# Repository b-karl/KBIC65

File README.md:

# KBIC65
A 65% [mechanical keyboard](https://keyboard.university/100-courses/intro-to-mechanical-keyboards) with a [ProMicro](https://deskthority.net/wiki/Arduino_Pro_Micro) controller footprint. Repository contains [KiCad](https://www.kicad.org/) PCB design files and 2D drawings in SVG of PCB, bottom plate, switch plate and acrylic window.

Bottom of keyboard has two alternatives. A design with glass rims inspired by my grandfather's glasses and a dithered image of the sun from the [NASA Solar Dynamics Observatory](https://svs.gsfc.nasa.gov/13641). Included below is also a [guide on creating dithered PCB art](#making-dithered-pcb-art-for-kicad).

[More photos](img/photoshoot/readme.md)

# Main features/focus
- Intended to be portable and wireless, but with a [through-hole technology (THT)](https://en.wikipedia.org/wiki/Through-hole_technology) style
- 65%/70 key layout with spaced arrow keys and right-side navigation row in the style of [Satistifaction75](https://cannonkeys.com/collections/group-buy/products/gb-satisfaction-75-keyboard-round-2) and many others
- ProMicro footprint to allow upgrade of the microcontroller, intended to be used with the [nice!nano](https://nicekeyboards.com/nice-nano/) and [ZMK](https://zmkfirmware.dev/) firmware for my personal build
- Designed to be mountable in both an open PCB stack or in a plate-mounted case (not yet designed)
- 8x9 wiring [duplex matrix](https://wiki.ai03.com/books/pcb-design/page/matrices-and-duplex-matrix) requiring only 17 pins on a ProMicro compatible controller

# Some design choices

- Reduced copper coverage on top of PCB and bottom plate, and no copper switch plate to improve Bluetooth signal
- Plate mounted with screws, the PCB contains drilled holes large enough to fit M2 spacers. I.e. the PCB is only connected to the plate via the switches.
- Tried to avoid vias, but have one (that I probably could have skipped)
- Since the bottom is symmetrical, there are two alternative design two choose from

# How to create your own
[See the v1.0 release](https://github.com/b-karl/KBIC65/releases/tag/v1.0.0) to find the files and list of parts to create your own. 
- Gerber zip-files are used to order the PCB, bottom plate and top plate from a PCB manufacturer, I used [JLCPCB](https://jlcpcb.com/). 
- The acrylic window can be ordered from any laser cutting firm working with acrylic, I live in Sweden and used [TechStation](https://techstation.se/en/). 
- For keycaps, switches and ProMicro-compatible controller (possibly also diodes) use a keyboard company in your region, I got my keycaps from [KBDfans](https://kbdfans.com/), diodes from a local electronics supplier and the rest from [Splitkb](https://splitkb.com/).
- Screws and stand-offs can be sourced from various places but are probably easiest to find on AliExpress.

I do not have dedicated assembly instructions, but if you are comfortable soldering you can probably make do using [my build log](build_log.md).
# Firmware
I decided to use [ZMK](https://zmkfirmware.dev/) for my build of this keyboard. Compared to the most common open source mechanical keyboard firmware [QMK](https://docs.qmk.fm/#/), ZMK is tailored for wireless keyboards. The two main reasons you should care to use ZMK instead of a bluetooth QMK fork are (1) much better power efficiency, i.e. longer battery life, and (2) the most commonly used Bluetooth chip uses drivers that are not compatible with the QMK copyleft license.

You can find my ZMK shield for the KBIC65 in [my ZMK config repository](https://github.com/b-karl/zmk-config).

If you want to use a non-wireless controller (like a ProMicro, Elite-C etc.), I have [created a QMK fork](https://github.com/b-karl/qmk_firmware/tree/add-kbic65-keyboard/keyboards/karlb/kbic65) that has been tested on the KBIC65 using an Elite-C rev 4.

# Layout options

# Components

## PCB Front

## Plate

## Bottom Option 1 (PCB Front)

## Bottom Option 2 (PCB Back)

# Making dithered PCB art for KiCad
When I decided to make an alternative design for the bottom I eventually settled on trying my hand at a dithered image. This was a little trickier than I expected to get looking like I wanted (and still not sure how the end result will appear).

But generally here is the workflow I used in the end, and would recommend
- Settle on an image to use, crop it to only the part you want to place on the PCB. I settled on a NASA SDO image.

- JLCPCB and probably other PCB manufacturers can print at a resolution of about 0.15 mm which is equivalent to about 169 DPI. This means you should try to use 169 DPI or less, I used 169 DPI. Resize your image so that the resolution of the image at your selected DPI gives you the size you want on the board. I wanted my sun to be approximately 90 mm high so I resized to 600px high, which results in an image 90.2 mm high at 169 DPI. 

- Use a dithering tool to dither your image and create a dithered copy. I strongly recommend [Ditherlicious](https://29a.ch/ditherlicious/) but you can look around for other tools you have handy.

- Open your KiCad project and then open Convert Image, a.k.a. the bitmap2component tool.
- Import your dithered image, select Negative if necessary, pick either Front Silk Screen or Front Solder Mask and enter your chosen DPI. Click export and put into a new folder that will become a new KiCad library for you.
- In Pcbnew or your KiCad project, open Preferences > Manage footprint libraries
- Add your new folder as a footprint library
- Import your new PCB art footprint onto your PCB

- Iterate, I played a lot with different dithering tools, changing the image histogram etc. The bitmap2component tool does not import dithered image exactly but blends pixels together, therefore I would recommend generating a few variants and comparing them in KiCad and possibly the 3D viewer. Please note that these images requires quite a bit of processing from KiCad. Updating the 3D view especially, which took about 1-2 min for me.

- Final result after ordering from JLCPCB with black solder mask and ENIG finish

# Comparison to similar keyboards

## Discipline65
The [Discipline65](https://github.com/coseyfannitutti/discipline) is the original inspiration for this keyboard, along with the case making community that has been born around it. In the spirit of CFTKB the board design will also be open source.

Some of the main differences
- KBIC65 will use a dedicated ProMicro footprint instead of all the THT components in the Discipline65, a believe this makes the board more easy to upgrade at the cost of losing some of the THT aesthetic.
- The layers in the Discipline FR4 kit have the same outer dimension (excluding the top part of the plate), which is nice for a pure FR4-style keyboard but creates some limitations if one wants to create a case for it. The KBIC65 will have a minimal PCB given the layout (on the left, bottom and right sides) and a plate with overhang allowing for various types of plate-mounted case designs.
- The PCB will have holes large enough to fit M2 spacers between THT row and the layout. This allows the FR4 kit-style assembly to have the PCB completely free-floating and only the switch plate connecting directly to the bottom plate.

## Nibble65
The [Nibble65](https://nullbits.co/nibble/) is another board inspired by the Discipline65. It has an additional column of keys on the left, allowing also for rotary encoders and the top of this column houses a ProMicro footprint. 

Some differences
- The Nibble65 has similar limitations to the Discipline65 in terms of case design compatibility
- The Nibble65 uses multiplexers (I believe) to keep the PCB wiring simple and to add a bit to the THT aesthetic. The KBIC65 uses an efficient wiring matrix allowing for a full 65%/70 key layout without additional components.
- The Nibble65 has an extra column to the left, housing a ProMicro-footprint, some extra keys as well as a multi-purpose section for either rotary encodes, giant LED or an OLED screen.

# Possible future work
- Non-metal case
- Solar cell trickle charging panel instead of window
- Remove unintended silk screen from front PCB glasses
- Add holes for mounting a battery connector
- Move JLCPCB production number location (or get it removed in production)
- Change battery to something slightly thinner, sub-5 mm, but could be wider and longer than the current battery

# FAQ

### What does KBIC mean?
The original name KBIC65 is inspired by soldering and tinkering in my grandfather's workshop as a child and have named it with our combined initials KB and IC. But having spent quite a bit of time on making PCB art for the bottom of the keyboard based on an image from the [NASA Solar Dynamics Observatory](https://svs.gsfc.nasa.gov/13641) I am considering renaming it if I make anything more of it (or make a group buy at some point). I am open to name suggestions if you have one!

### Why don't you just buy keyboard X? It is cheaper and simpler than designing this.
I am doing this as a side project for fun, and the learning experience, and definitely not for profit.

If you want a 65% keyboard with the THT aesthetic get a [Discipline65](https://github.com/coseyfannitutti/discipline). If you want a 65% for your nice!nano, get the [Nibble65](https://nullbits.co/nibble/). If you just want something wireless but don't want to build it yourself, get a [Keychron](https://www.keychron.com/).

### I really want to make one myself, can you please fix the remaining issues?
Maybe, if you have some experience or willingness to learn, fork this repo and try to fix it yourself (and maybe do a PR on the end result). If you don't have the experience or know-how, send me a message so I know someone actually wants it and I will consider fixing it when I have time.

### This is just a rip-off of keyboard X. What gives?
I am trying to make my own thing but the design is of course heavily inspired by other keyboards, especially THT kits. Some honorable mentions

- [Nicell Dissatisfaction65](https://github.com/Nicell/Dissatisfaction-65)
A very similar keyboard to what I am designing, by the creator of the nice!nano. This uses a lot of the "early" techniques for what I feel a wireless open-source firmware was in 2019-beginning of 2020 such as Adafruit Feather BLE with QMK, something that is much better done today with the nice!nano (and similar controllers) and the ZMK firmware. Nicell is the creator of the nice!nano and also very active in the ZMK project.

- [CannonKeys Satisfaction75](https://ilumkb.com/blogs/news/satisfaction-75-r2)
My original inspiration for the layout

- [CFTKB Discipline65](https://github.com/coseyfannitutti/discipline)
Original inspiration for the THT design and the idea to make an FR4 kit first and a case after. The open-source Kicad files have also been a good sanity check, plus it has beautiful wiring!

- [Nullbits Nibble65](https://nullbits.co/nibble/)
A great take on the THT and would be my choice to buy if I didn't want to make something of my own but still make a nice!nano keyboard.

- [Lysol LCK75](https://p3dstore.com/products/lck75): No diode row but THT components otherwise and that arrow keys and navigation column stagger.

- [MujiManic Disarray65](https://sneakbox.com/products/disarray): Not exactly THT, but sooo much fun, beautiful wiring and one of the best case ideas ever. Case also comes in a version for the Discipline.

- [RMI-KB Herringbone75](https://rmi-kb.com/herringbone/): A fun variant on the Mysterium 75.

- [u/emdarcher Lattice 60%](https://keyhive.xyz/shop/lattice): Definitely contender for most innovative diode placement among THT keyboards

- [theksmith Discipline65](https://theksmith.com/hardware/designing-building-custom-mechanical-keyboard-2020/): Honorable mention on Discipline65 case design

- [4Bar60 by u/struct_Nodes](https://www.reddit.com/r/MechanicalKeyboards/comments/kyjpx3/my_girlfriend_surprised_me_with_a_breakup_before/)
I found this keyboard in the middle of my PCB design but it is very similar to my intended design, except being a 60% of course.

- [WorldspawnsKeebs Houndstooth](https://www.etsy.com/uk/listing/717316405/houndstooth-kit-does-not-include?show_sold_out_detail=1&ref=nla_listing_details)
A split ortholinear 4x6 with a nice take on a clear case

- [Seoulcialite Argyle60](https://geekhack.org/index.php?topic=106255.0)
Great case for a THT kit and very interesting with side windows instead of placed above the key layout. Inspiration for moving the ProMicro footprint and diode row up 1/4 units to allow top case to have a divider between main layout and THT window.

- [EBastler Isometria75](https://github.com/ebastler/isometria-75)
Makes me want to try to change the key spacing on my keyboard, but I am unfortunately not brave enough.

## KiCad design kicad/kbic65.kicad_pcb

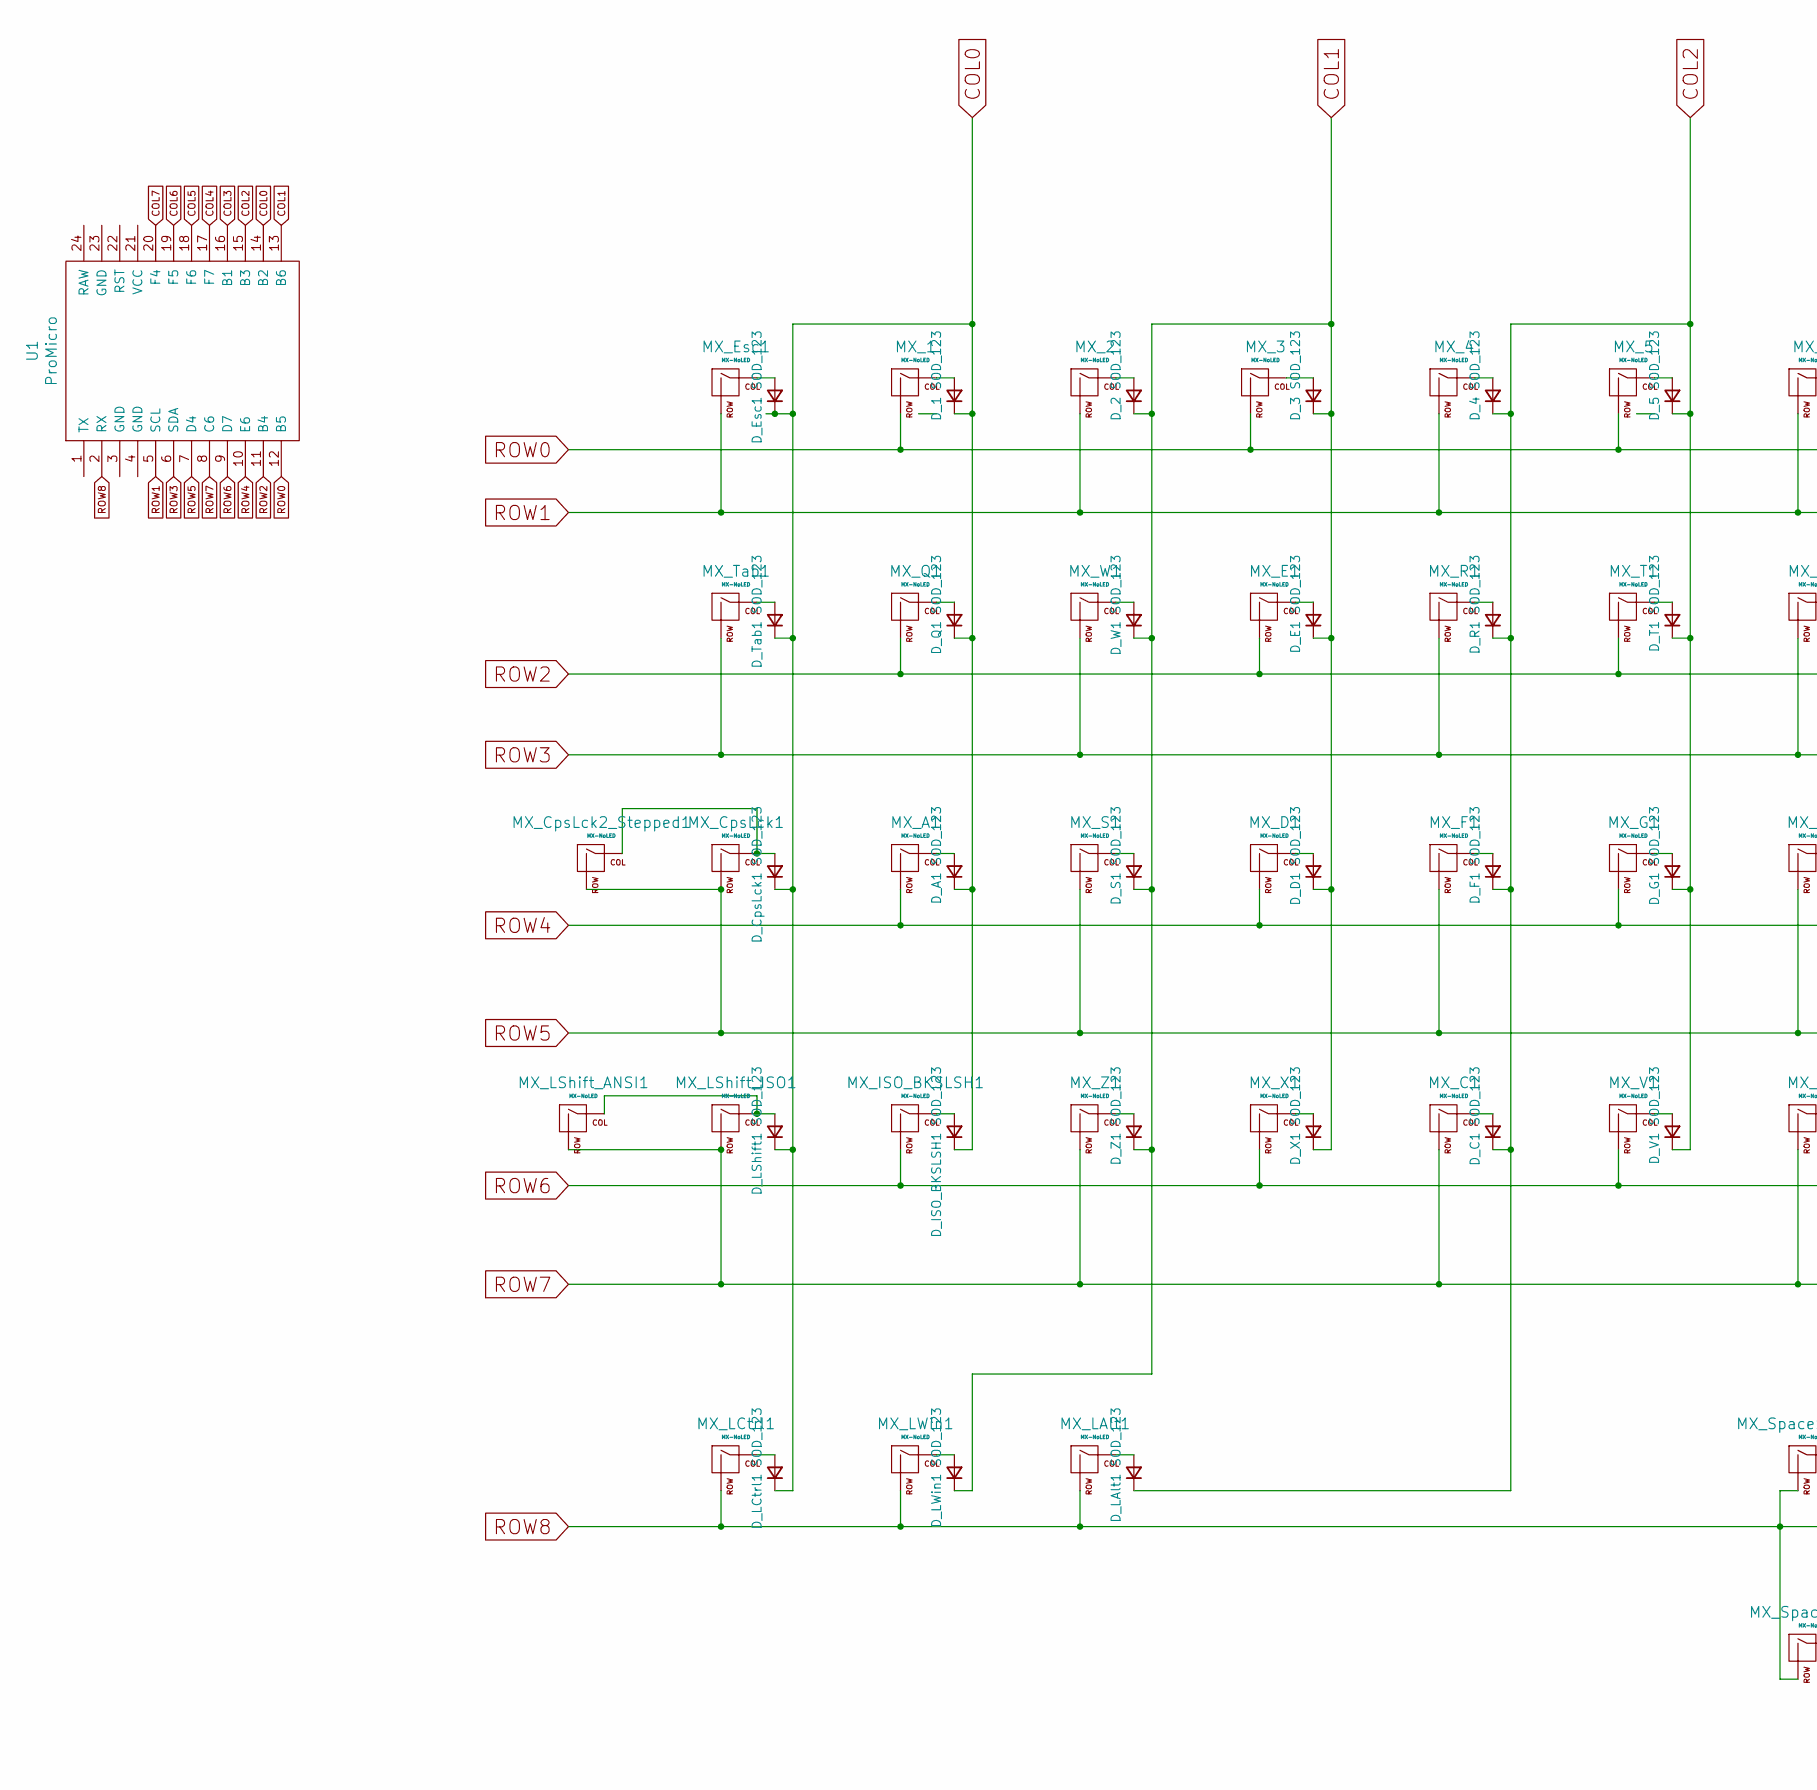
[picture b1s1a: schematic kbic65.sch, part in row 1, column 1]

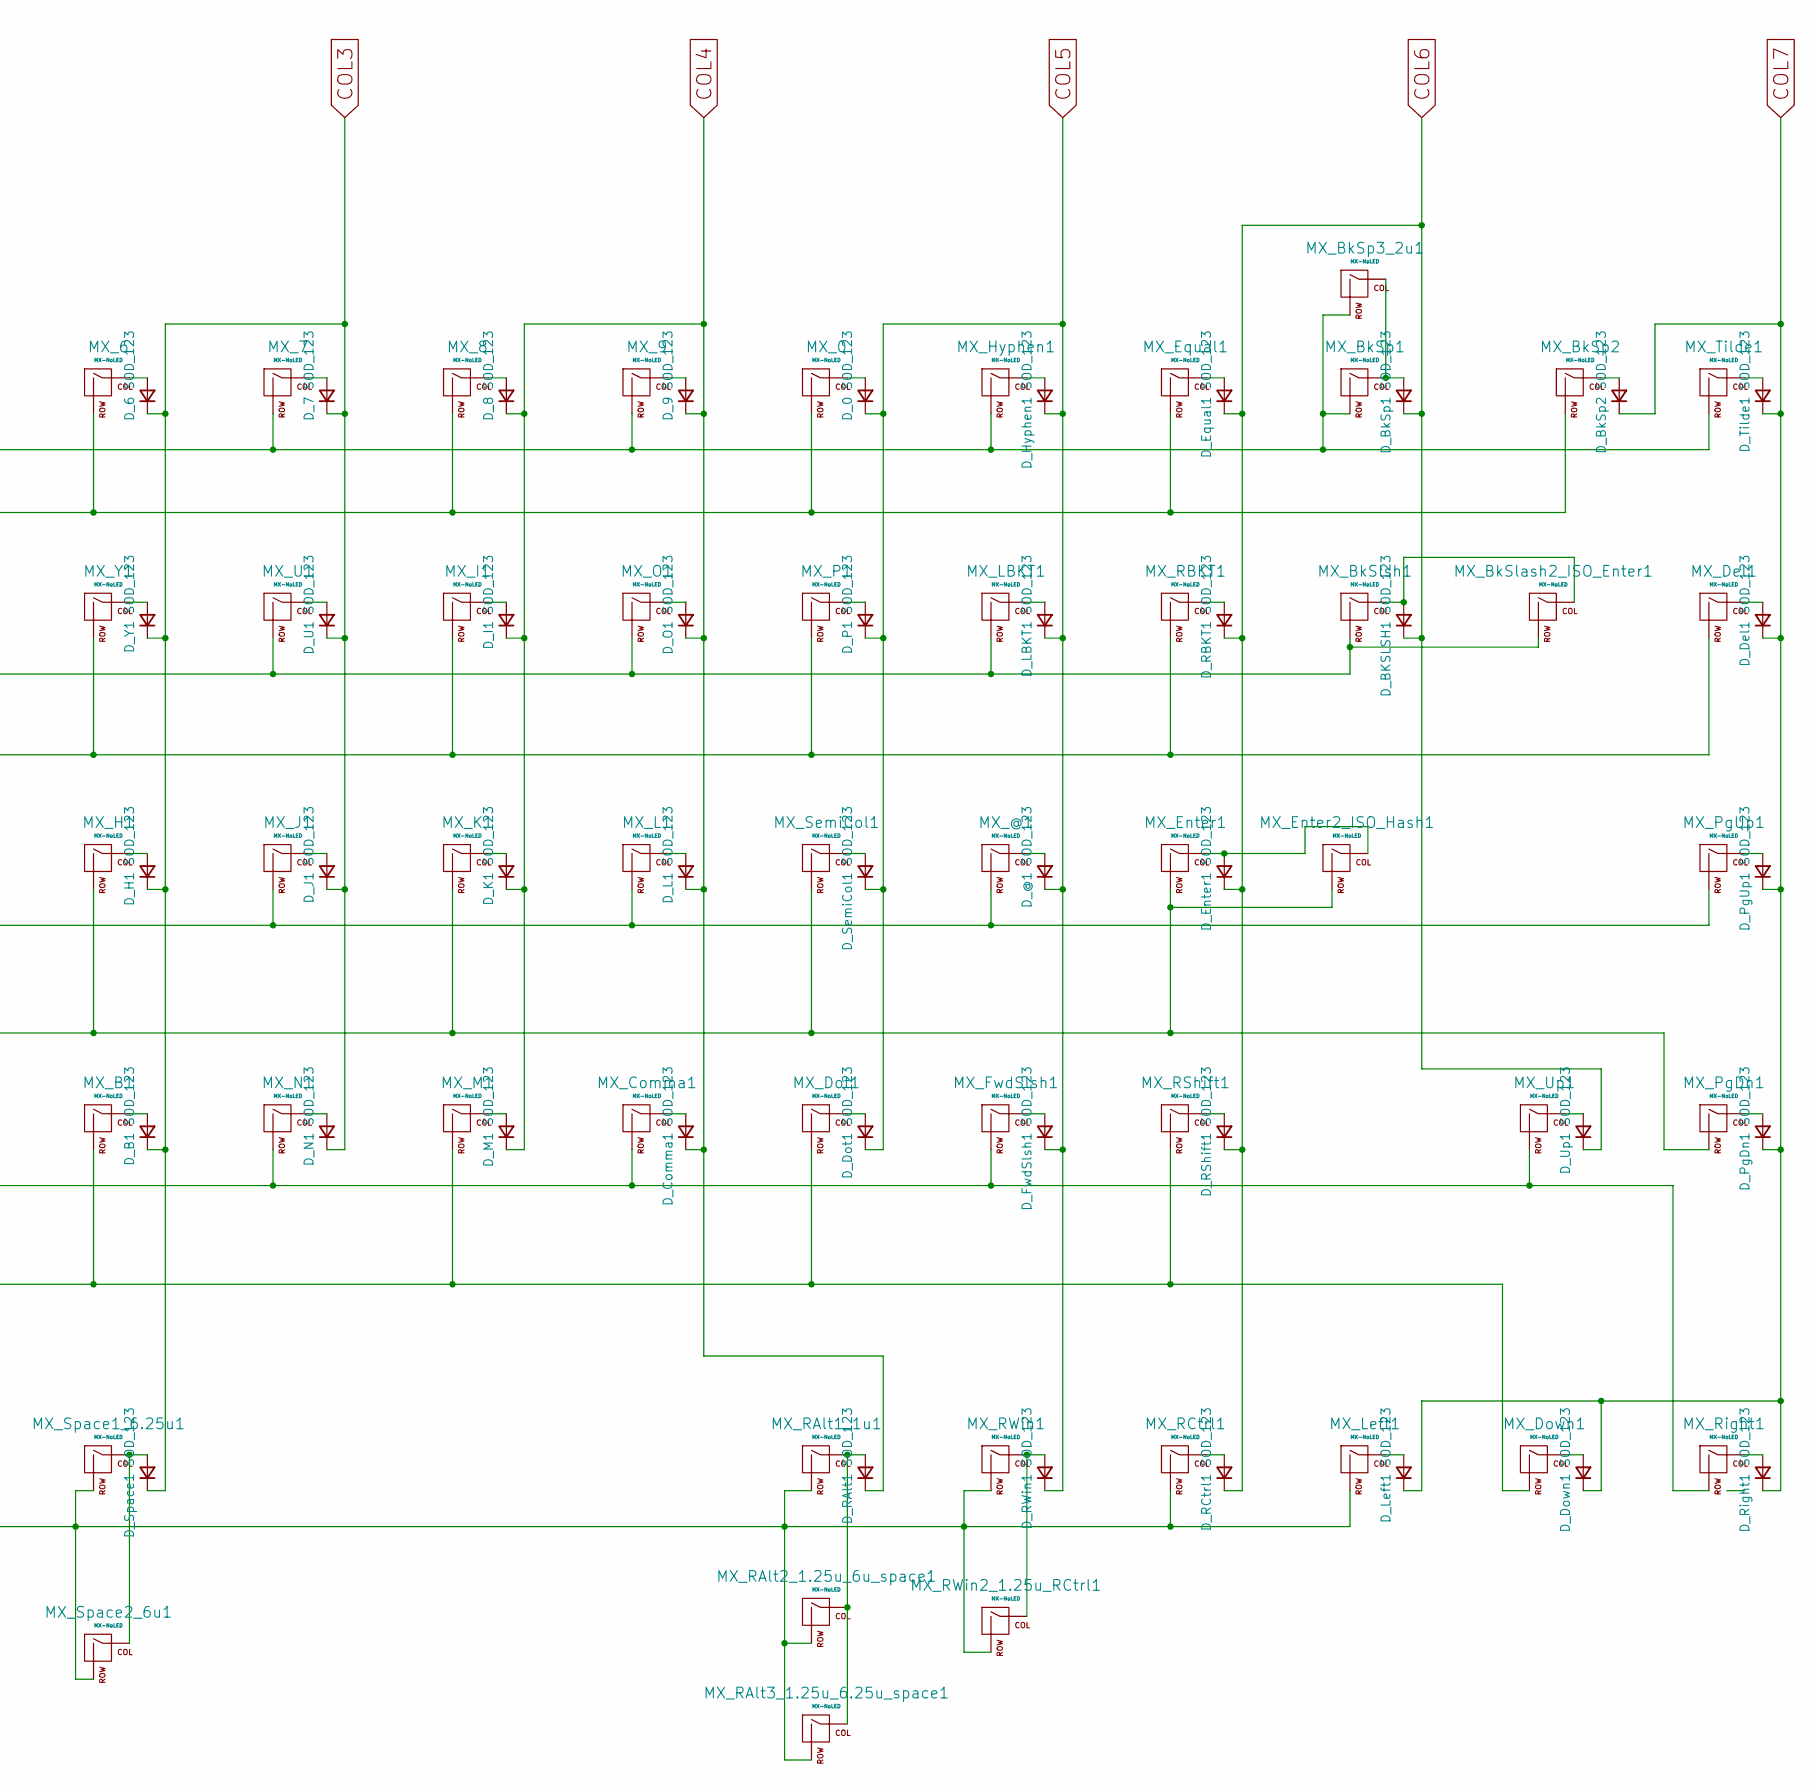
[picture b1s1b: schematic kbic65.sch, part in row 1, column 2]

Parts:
D_0, D_1, D_2, D_3, D_4, D_5, D_6, D_7, D_8, D_9: SOD_123; D_DO-35_SOD27_P5.08mm_Vertical_AnodeUp
D_@1: SOD_123; D_DO-35_SOD27_P5.08mm_Vertical_AnodeUp
D_A1: SOD_123; D_DO-35_SOD27_P5.08mm_Vertical_AnodeUp
D_B1: SOD_123; D_DO-35_SOD27_P5.08mm_Vertical_AnodeUp
D_BKSLSH1: SOD_123; D_DO-35_SOD27_P5.08mm_Vertical_AnodeUp
D_BkSp1, D_BkSp2: SOD_123; D_DO-35_SOD27_P5.08mm_Vertical_AnodeUp
D_C1: SOD_123; D_DO-35_SOD27_P5.08mm_Vertical_AnodeUp
D_Comma1: SOD_123; D_DO-35_SOD27_P5.08mm_Vertical_AnodeUp
D_CpsLck1: SOD_123; D_DO-35_SOD27_P5.08mm_Vertical_AnodeUp
D_D1: SOD_123; D_DO-35_SOD27_P5.08mm_Vertical_AnodeUp
D_Del1: SOD_123; D_DO-35_SOD27_P5.08mm_Vertical_AnodeUp
D_Dot1: SOD_123; D_DO-35_SOD27_P5.08mm_Vertical_AnodeUp
D_Down1: SOD_123; D_DO-35_SOD27_P5.08mm_Vertical_AnodeUp
D_E1: SOD_123; D_DO-35_SOD27_P5.08mm_Vertical_AnodeUp
D_Enter1: SOD_123; D_DO-35_SOD27_P5.08mm_Vertical_AnodeUp
D_Equal1: SOD_123; D_DO-35_SOD27_P5.08mm_Vertical_AnodeUp
D_Esc1: SOD_123; D_DO-35_SOD27_P5.08mm_Vertical_AnodeUp
D_F1: SOD_123; D_DO-35_SOD27_P5.08mm_Vertical_AnodeUp
D_FwdSlsh1: SOD_123; D_DO-35_SOD27_P5.08mm_Vertical_AnodeUp
D_G1: SOD_123; D_DO-35_SOD27_P5.08mm_Vertical_AnodeUp
D_H1: SOD_123; D_DO-35_SOD27_P5.08mm_Vertical_AnodeUp
D_Hyphen1: SOD_123; D_DO-35_SOD27_P5.08mm_Vertical_AnodeUp
D_I1: SOD_123; D_DO-35_SOD27_P5.08mm_Vertical_AnodeUp
D_ISO_BKSLSH1: SOD_123; D_DO-35_SOD27_P5.08mm_Vertical_AnodeUp
D_J1: SOD_123; D_DO-35_SOD27_P5.08mm_Vertical_AnodeUp
D_K1: SOD_123; D_DO-35_SOD27_P5.08mm_Vertical_AnodeUp
D_L1: SOD_123; D_DO-35_SOD27_P5.08mm_Vertical_AnodeUp
D_LAlt1: SOD_123; D_DO-35_SOD27_P5.08mm_Vertical_AnodeUp
D_LBKT1: SOD_123; D_DO-35_SOD27_P5.08mm_Vertical_AnodeUp
D_LCtrl1: SOD_123; D_DO-35_SOD27_P5.08mm_Vertical_AnodeUp
D_LShift1: SOD_123; D_DO-35_SOD27_P5.08mm_Vertical_AnodeUp
D_LWin1: SOD_123; D_DO-35_SOD27_P5.08mm_Vertical_AnodeUp
D_Left1: SOD_123; D_DO-35_SOD27_P5.08mm_Vertical_AnodeUp
D_M1: SOD_123; D_DO-35_SOD27_P5.08mm_Vertical_AnodeUp
D_N1: SOD_123; D_DO-35_SOD27_P5.08mm_Vertical_AnodeUp
D_O1: SOD_123; D_DO-35_SOD27_P5.08mm_Vertical_AnodeUp
D_P1: SOD_123; D_DO-35_SOD27_P5.08mm_Vertical_AnodeUp
D_PgDn1: SOD_123; D_DO-35_SOD27_P5.08mm_Vertical_AnodeUp
D_PgUp1: SOD_123; D_DO-35_SOD27_P5.08mm_Vertical_AnodeUp
D_Q1: SOD_123; D_DO-35_SOD27_P5.08mm_Vertical_AnodeUp
D_R1: SOD_123; D_DO-35_SOD27_P5.08mm_Vertical_AnodeUp
D_RAlt1: SOD_123; D_DO-35_SOD27_P5.08mm_Vertical_AnodeUp
D_RBKT1: SOD_123; D_DO-35_SOD27_P5.08mm_Vertical_AnodeUp
D_RCtrl1: SOD_123; D_DO-35_SOD27_P5.08mm_Vertical_AnodeUp
D_RShift1: SOD_123; D_DO-35_SOD27_P5.08mm_Vertical_AnodeUp
D_RWin1: SOD_123; D_DO-35_SOD27_P5.08mm_Vertical_AnodeUp
D_Right1: SOD_123; D_DO-35_SOD27_P5.08mm_Vertical_AnodeUp
D_S1: SOD_123; D_DO-35_SOD27_P5.08mm_Vertical_AnodeUp
D_SemiCol1: SOD_123; D_DO-35_SOD27_P5.08mm_Vertical_AnodeUp
D_Space1: SOD_123; D_DO-35_SOD27_P5.08mm_Vertical_AnodeUp
D_T1: SOD_123; D_DO-35_SOD27_P5.08mm_Vertical_AnodeUp
D_Tab1: SOD_123; D_DO-35_SOD27_P5.08mm_Vertical_AnodeUp
D_Tilde1: SOD_123; D_DO-35_SOD27_P5.08mm_Vertical_AnodeUp
D_U1: SOD_123; D_DO-35_SOD27_P5.08mm_Vertical_AnodeUp
D_Up1: SOD_123; D_DO-35_SOD27_P5.08mm_Vertical_AnodeUp
D_V1: SOD_123; D_DO-35_SOD27_P5.08mm_Vertical_AnodeUp
D_W1: SOD_123; D_DO-35_SOD27_P5.08mm_Vertical_AnodeUp
D_X1: SOD_123; D_DO-35_SOD27_P5.08mm_Vertical_AnodeUp
D_Y1: SOD_123; D_DO-35_SOD27_P5.08mm_Vertical_AnodeUp
D_Z1: SOD_123; D_DO-35_SOD27_P5.08mm_Vertical_AnodeUp
MX_0, MX_1, MX_2, MX_3, MX_4, MX_5, MX_6, MX_7, MX_8, MX_9: MX-NoLED; MXOnly-1U-NoLED
MX_@1: MX-NoLED; MXOnly-1U-NoLED
MX_A1: MX-NoLED; MXOnly-1U-NoLED
MX_B1: MX-NoLED; MXOnly-1U-NoLED
MX_BkSlash2_ISO_Enter1: MX-NoLED; MXOnly-ISO-ROTATED-ReversedStabilizers-NoLED
MX_BkSlsh1: MX-NoLED; MXOnly-1.5U-NoLED
MX_BkSp1, MX_BkSp2: MX-NoLED; MXOnly-1U-NoLED
MX_BkSp3_2u1: MX-NoLED; MXOnly-2U-NoLED
MX_C1: MX-NoLED; MXOnly-1U-NoLED
MX_Comma1: MX-NoLED; MXOnly-1U-NoLED
MX_CpsLck1: MX-NoLED; MXOnly-1.75U-NoLED
MX_CpsLck2_Stepped1: MX-NoLED; MXOnly-1.25U-NoLED
MX_D1: MX-NoLED; MXOnly-1U-NoLED
MX_Del1: MX-NoLED; MXOnly-1U-NoLED
MX_Dot1: MX-NoLED; MXOnly-1U-NoLED
MX_Down1: MX-NoLED; MXOnly-1U-NoLED
MX_E1: MX-NoLED; MXOnly-1U-NoLED
MX_Enter1: MX-NoLED; MXOnly-2.25U-NoLED
MX_Enter2_ISO_Hash1: MX-NoLED; MXOnly-1U-NoLED
MX_Equal1: MX-NoLED; MXOnly-1U-NoLED
MX_Esc1: MX-NoLED; MXOnly-1U-NoLED
MX_F1: MX-NoLED; MXOnly-1U-NoLED
MX_FwdSlsh1: MX-NoLED; MXOnly-1U-NoLED
MX_G1: MX-NoLED; MXOnly-1U-NoLED
MX_H1: MX-NoLED; MXOnly-1U-NoLED
MX_Hyphen1: MX-NoLED; MXOnly-1U-NoLED
MX_I1: MX-NoLED; MXOnly-1U-NoLED
MX_ISO_BKSLSH1: MX-NoLED; MXOnly-1U-NoLED
MX_J1: MX-NoLED; MXOnly-1U-NoLED
MX_K1: MX-NoLED; MXOnly-1U-NoLED
MX_L1: MX-NoLED; MXOnly-1U-NoLED
MX_LAlt1: MX-NoLED; MXOnly-1.25U-NoLED
MX_LBKT1: MX-NoLED; MXOnly-1U-NoLED
MX_LCtrl1: MX-NoLED; MXOnly-1.25U-NoLED
MX_LShift_ANSI1: MX-NoLED; MXOnly-2.25U-NoLED
MX_LShift_ISO1: MX-NoLED; MXOnly-1.25U-NoLED
MX_LWin1: MX-NoLED; MXOnly-1.25U-NoLED
MX_Left1: MX-NoLED; MXOnly-1U-NoLED
MX_M1: MX-NoLED; MXOnly-1U-NoLED
MX_N1: MX-NoLED; MXOnly-1U-NoLED
MX_O1: MX-NoLED; MXOnly-1U-NoLED
MX_P1: MX-NoLED; MXOnly-1U-NoLED
MX_PgDn1: MX-NoLED; MXOnly-1U-NoLED
MX_PgUp1: MX-NoLED; MXOnly-1U-NoLED
MX_Q1: MX-NoLED; MXOnly-1U-NoLED
MX_R1: MX-NoLED; MXOnly-1U-NoLED
MX_RAlt1_1u1: MX-NoLED; MXOnly-1U-NoLED
MX_RAlt2_1.25u_6u_space1, MX_RAlt3_1.25u_6.25u_space1: MX-NoLED; MXOnly-1.25U-NoLED
MX_RBKT1: MX-NoLED; MXOnly-1U-NoLED
MX_RCtrl1: MX-NoLED; MXOnly-1U-NoLED
MX_RShift1: MX-NoLED; MXOnly-1.75U-NoLED
MX_RWin1, MX_RWin2_1.25u_RCtrl1: MX-NoLED; MXOnly-1U-NoLED
MX_Right1: MX-NoLED; MXOnly-1U-NoLED
MX_S1: MX-NoLED; MXOnly-1U-NoLED
MX_SemiCol1: MX-NoLED; MXOnly-1U-NoLED
MX_Space1_6.25u1: MX-NoLED; MXOnly-6.25U-NoLED
MX_Space2_6u1: MX-NoLED; MXOnly-6U-Centered-NoLED
MX_T1: MX-NoLED; MXOnly-1U-NoLED
MX_Tab1: MX-NoLED; MXOnly-1.5U-NoLED
MX_Tilde1: MX-NoLED; MXOnly-1U-NoLED
MX_U1: MX-NoLED; MXOnly-1U-NoLED
MX_Up1: MX-NoLED; MXOnly-1U-NoLED
MX_V1: MX-NoLED; MXOnly-1U-NoLED
MX_W1: MX-NoLED; MXOnly-1U-NoLED
MX_X1: MX-NoLED; MXOnly-1U-NoLED
MX_Y1: MX-NoLED; MXOnly-1U-NoLED
MX_Z1: MX-NoLED; MXOnly-1U-NoLED
U1: ProMicro; ArduinoProMicro-ZigZag

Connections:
COL0: D_1.1 (K), D_A1.1 (K), D_CpsLck1.1 (K), D_Esc1.1 (K), D_ISO_BKSLSH1.1 (K), D_LCtrl1.1 (K), D_LShift1.1 (K), D_Q1.1 (K), D_Tab1.1 (K), U1.14 (B2)
COL1: D_2.1 (K), D_3.1 (K), D_D1.1 (K), D_E1.1 (K), D_LWin1.1 (K), D_S1.1 (K), D_W1.1 (K), D_X1.1 (K), D_Z1.1 (K), U1.13 (B6)
COL2: D_4.1 (K), D_5.1 (K), D_C1.1 (K), D_F1.1 (K), D_G1.1 (K), D_LAlt1.1 (K), D_R1.1 (K), D_T1.1 (K), D_V1.1 (K), U1.15 (B3)
COL3: D_6.1 (K), D_7.1 (K), D_B1.1 (K), D_H1.1 (K), D_J1.1 (K), D_N1.1 (K), D_Space1.1 (K), D_U1.1 (K), D_Y1.1 (K), U1.16 (B1)
COL4: D_8.1 (K), D_9.1 (K), D_Comma1.1 (K), D_I1.1 (K), D_K1.1 (K), D_L1.1 (K), D_M1.1 (K), D_O1.1 (K), D_RAlt1.1 (K), U1.17 (F7)
COL5: D_0.1 (K), D_@1.1 (K), D_Dot1.1 (K), D_FwdSlsh1.1 (K), D_Hyphen1.1 (K), D_LBKT1.1 (K), D_P1.1 (K), D_RWin1.1 (K), D_SemiCol1.1 (K), U1.18 (F6)
COL6: D_BKSLSH1.1 (K), D_BkSp1.1 (K), D_Enter1.1 (K), D_Equal1.1 (K), D_RBKT1.1 (K), D_RCtrl1.1 (K), D_RShift1.1 (K), D_Up1.1 (K), U1.19 (F5)
COL7: D_BkSp2.1 (K), D_Del1.1 (K), D_Down1.1 (K), D_Left1.1 (K), D_PgDn1.1 (K), D_PgUp1.1 (K), D_Right1.1 (K), D_Tilde1.1 (K), U1.20 (F4)
GND: U1.3 (GND), U1.4 (GND), U1.23 (GND)
unnamed: D_0.2 (A), MX_0.1 (COL)
unnamed: D_1.2 (A), MX_1.1 (COL)
unnamed: D_2.2 (A), MX_2.1 (COL)
unnamed: D_3.2 (A), MX_3.1 (COL)
unnamed: D_4.2 (A), MX_4.1 (COL)
unnamed: D_5.2 (A), MX_5.1 (COL)
unnamed: D_6.2 (A), MX_6.1 (COL)
unnamed: D_7.2 (A), MX_7.1 (COL)
unnamed: D_8.2 (A), MX_8.1 (COL)
unnamed: D_9.2 (A), MX_9.1 (COL)
unnamed: D_@1.2 (A), MX_@1.1 (COL)
unnamed: D_A1.2 (A), MX_A1.1 (COL)
unnamed: D_B1.2 (A), MX_B1.1 (COL)
unnamed: D_BKSLSH1.2 (A), MX_BkSlash2_ISO_Enter1.1 (COL), MX_BkSlsh1.1 (COL)
unnamed: D_BkSp1.2 (A), MX_BkSp1.1 (COL), MX_BkSp3_2u1.1 (COL)
unnamed: D_BkSp2.2 (A), MX_BkSp2.1 (COL)
unnamed: D_C1.2 (A), MX_C1.1 (COL)
unnamed: D_Comma1.2 (A), MX_Comma1.1 (COL)
unnamed: D_CpsLck1.2 (A), MX_CpsLck1.1 (COL), MX_CpsLck2_Stepped1.1 (COL)
unnamed: D_D1.2 (A), MX_D1.1 (COL)
unnamed: D_Del1.2 (A), MX_Del1.1 (COL)
unnamed: D_Dot1.2 (A), MX_Dot1.1 (COL)
unnamed: D_Down1.2 (A), MX_Down1.1 (COL)
unnamed: D_E1.2 (A), MX_E1.1 (COL)
unnamed: D_Enter1.2 (A), MX_Enter1.1 (COL), MX_Enter2_ISO_Hash1.1 (COL)
unnamed: D_Equal1.2 (A), MX_Equal1.1 (COL)
unnamed: D_Esc1.2 (A), MX_Esc1.1 (COL)
unnamed: D_F1.2 (A), MX_F1.1 (COL)
unnamed: D_FwdSlsh1.2 (A), MX_FwdSlsh1.1 (COL)
unnamed: D_G1.2 (A), MX_G1.1 (COL)
unnamed: D_H1.2 (A), MX_H1.1 (COL)
unnamed: D_Hyphen1.2 (A), MX_Hyphen1.1 (COL)
unnamed: D_I1.2 (A), MX_I1.1 (COL)
unnamed: D_ISO_BKSLSH1.2 (A), MX_ISO_BKSLSH1.1 (COL)
unnamed: D_J1.2 (A), MX_J1.1 (COL)
unnamed: D_K1.2 (A), MX_K1.1 (COL)
unnamed: D_L1.2 (A), MX_L1.1 (COL)
unnamed: D_LAlt1.2 (A), MX_LAlt1.1 (COL)
unnamed: D_LBKT1.2 (A), MX_LBKT1.1 (COL)
unnamed: D_LCtrl1.2 (A), MX_LCtrl1.1 (COL)
unnamed: D_LShift1.2 (A), MX_LShift_ANSI1.1 (COL), MX_LShift_ISO1.1 (COL)
unnamed: D_LWin1.2 (A), MX_LWin1.1 (COL)
unnamed: D_Left1.2 (A), MX_Left1.1 (COL)
unnamed: D_M1.2 (A), MX_M1.1 (COL)
unnamed: D_N1.2 (A), MX_N1.1 (COL)
unnamed: D_O1.2 (A), MX_O1.1 (COL)
unnamed: D_P1.2 (A), MX_P1.1 (COL)
unnamed: D_PgDn1.2 (A), MX_PgDn1.1 (COL)
unnamed: D_PgUp1.2 (A), MX_PgUp1.1 (COL)
unnamed: D_Q1.2 (A), MX_Q1.1 (COL)
unnamed: D_R1.2 (A), MX_R1.1 (COL)
unnamed: D_RAlt1.2 (A), MX_RAlt1_1u1.1 (COL), MX_RAlt2_1.25u_6u_space1.1 (COL), MX_RAlt3_1.25u_6.25u_space1.1 (COL)
unnamed: D_RBKT1.2 (A), MX_RBKT1.1 (COL)
unnamed: D_RCtrl1.2 (A), MX_RCtrl1.1 (COL)
unnamed: D_RShift1.2 (A), MX_RShift1.1 (COL)
unnamed: D_RWin1.2 (A), MX_RWin1.1 (COL), MX_RWin2_1.25u_RCtrl1.1 (COL)
unnamed: D_Right1.2 (A), MX_Right1.1 (COL)
unnamed: D_S1.2 (A), MX_S1.1 (COL)
unnamed: D_SemiCol1.2 (A), MX_SemiCol1.1 (COL)
unnamed: D_Space1.2 (A), MX_Space1_6.25u1.1 (COL), MX_Space2_6u1.1 (COL)
unnamed: D_T1.2 (A), MX_T1.1 (COL)
unnamed: D_Tab1.2 (A), MX_Tab1.1 (COL)
unnamed: D_Tilde1.2 (A), MX_Tilde1.1 (COL)
unnamed: D_U1.2 (A), MX_U1.1 (COL)
unnamed: D_Up1.2 (A), MX_Up1.1 (COL)
unnamed: D_V1.2 (A), MX_V1.1 (COL)
unnamed: D_W1.2 (A), MX_W1.1 (COL)
unnamed: D_X1.2 (A), MX_X1.1 (COL)
unnamed: D_Y1.2 (A), MX_Y1.1 (COL)
unnamed: D_Z1.2 (A), MX_Z1.1 (COL)
ROW0: MX_1.2 (ROW), MX_3.2 (ROW), MX_5.2 (ROW), MX_7.2 (ROW), MX_9.2 (ROW), MX_BkSp1.2 (ROW), MX_BkSp3_2u1.2 (ROW), MX_Hyphen1.2 (ROW), MX_Tilde1.2 (ROW), U1.12 (B5)
ROW1: MX_0.2 (ROW), MX_2.2 (ROW), MX_4.2 (ROW), MX_6.2 (ROW), MX_8.2 (ROW), MX_BkSp2.2 (ROW), MX_Equal1.2 (ROW), MX_Esc1.2 (ROW), U1.5 (SCL)
ROW2: MX_BkSlash2_ISO_Enter1.2 (ROW), MX_BkSlsh1.2 (ROW), MX_E1.2 (ROW), MX_LBKT1.2 (ROW), MX_O1.2 (ROW), MX_Q1.2 (ROW), MX_T1.2 (ROW), MX_U1.2 (ROW), U1.11 (B4)
ROW3: MX_Del1.2 (ROW), MX_I1.2 (ROW), MX_P1.2 (ROW), MX_R1.2 (ROW), MX_RBKT1.2 (ROW), MX_Tab1.2 (ROW), MX_W1.2 (ROW), MX_Y1.2 (ROW), U1.6 (SDA)
ROW4: MX_@1.2 (ROW), MX_A1.2 (ROW), MX_D1.2 (ROW), MX_G1.2 (ROW), MX_J1.2 (ROW), MX_L1.2 (ROW), MX_PgUp1.2 (ROW), U1.10 (E6)
ROW5: MX_CpsLck1.2 (ROW), MX_CpsLck2_Stepped1.2 (ROW), MX_Enter1.2 (ROW), MX_Enter2_ISO_Hash1.2 (ROW), MX_F1.2 (ROW), MX_H1.2 (ROW), MX_K1.2 (ROW), MX_PgDn1.2 (ROW), MX_S1.2 (ROW), MX_SemiCol1.2 (ROW), U1.7 (D4)
ROW6: MX_Comma1.2 (ROW), MX_FwdSlsh1.2 (ROW), MX_ISO_BKSLSH1.2 (ROW), MX_N1.2 (ROW), MX_Right1.2 (ROW), MX_Up1.2 (ROW), MX_V1.2 (ROW), MX_X1.2 (ROW), U1.9 (D7)
ROW7: MX_B1.2 (ROW), MX_C1.2 (ROW), MX_Dot1.2 (ROW), MX_Down1.2 (ROW), MX_LShift_ANSI1.2 (ROW), MX_LShift_ISO1.2 (ROW), MX_M1.2 (ROW), MX_RShift1.2 (ROW), MX_Z1.2 (ROW), U1.8 (C6)
ROW8: MX_LAlt1.2 (ROW), MX_LCtrl1.2 (ROW), MX_LWin1.2 (ROW), MX_Left1.2 (ROW), MX_RAlt1_1u1.2 (ROW), MX_RAlt2_1.25u_6u_space1.2 (ROW), MX_RAlt3_1.25u_6.25u_space1.2 (ROW), MX_RCtrl1.2 (ROW), MX_RWin1.2 (ROW), MX_RWin2_1.25u_RCtrl1.2 (ROW), MX_Space1_6.25u1.2 (ROW), MX_Space2_6u1.2 (ROW), U1.2 (RX)

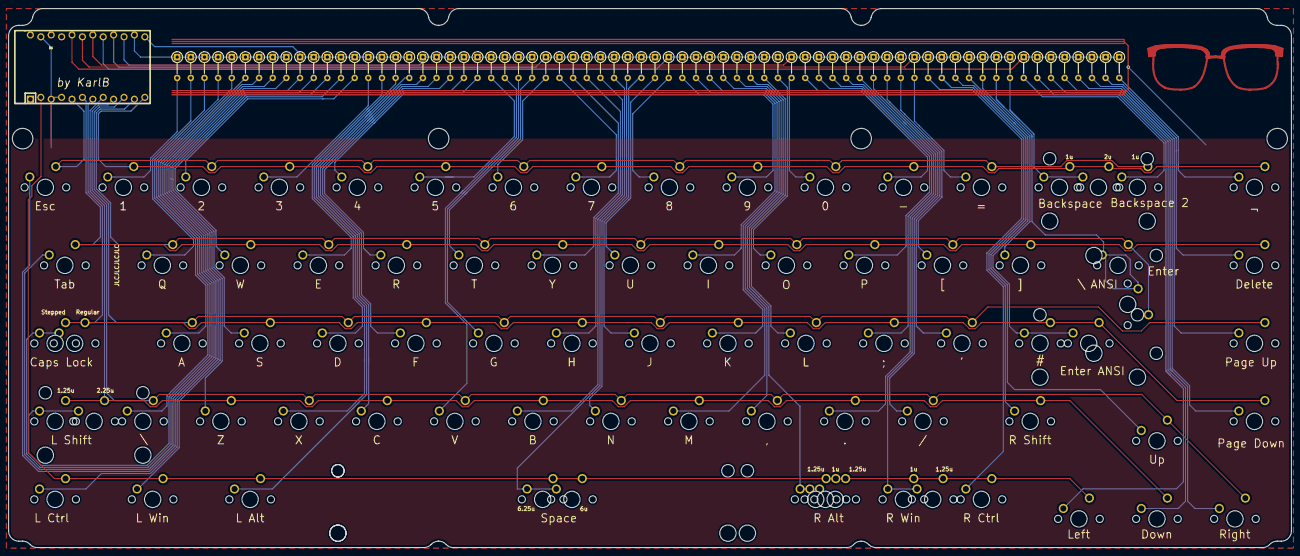
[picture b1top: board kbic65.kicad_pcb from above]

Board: 2 copper layers, 313.3 x 131.6 mm, 150 parts (0 on the bottom side), 88 nets.

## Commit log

2020-11-08 Created project
2020-11-08 Added submodules
2020-11-08 Added kebbio footprints
2020-11-08 added libraries to kicad
2020-11-08 added pro micro to kicad
2020-11-08 started working
2020-11-09 saved work in kicad
2020-12-07 Added key matrix
2020-12-12 Created new matrix and labeled ProMicro footprint
2020-12-12 Naming matrix components
2020-12-13 Added footprints
2020-12-14 Placed components on PCB and imported dxf
2020-12-14 Added and updated footprints
2020-12-16 Redrew schematic with all extra footprints
2020-12-16 Changed layout to top windows and rearranging diodes
2020-12-17 Changed diode to row2col instead to make better wiring, rearranging diode footprints
2020-12-19 Rearranged diodes for wiring
2020-12-19 Rearranged rows on promicro footprint
2020-12-19 Simple arrangement of diodes
2020-12-22 Reverted back to single line of diodes
2021-01-13 Changed outline to inkscape generated and aligned it
2021-01-13 Finally started wiring
2021-01-20 Changed structure of repo
2021-01-20 Added layout options
2021-01-20 Add isometria to readme
2021-01-20 More wiring
2021-01-21 Sooo much wiring
2021-01-22 Wiring 4 life
2021-01-22 added image
2021-01-23 Completed first version of full wiring
2021-01-24 Cleared wiring, starting over with default tracks
2021-01-24 Starting new wiring
2021-01-26 Updated wiring, added drill holes and cut outline
2021-01-27 Fixed 6u spacebar
2021-01-27 Moved drawings to git
2021-01-27 Merged all cutouts and added fillets in plate
2021-01-27 Thinking about plate size, added current state of pcb
2021-01-28 Drew first version of plate
2021-01-28 Fixed temp file
2021-02-01 Fixed with bottom plate
2021-02-07 Changing corners
2021-02-10 settled on top width
2021-02-11 pretty happy with window size
2021-02-15 Updated board design and rewired, starting silkscreens
2021-02-15 moved some references
2021-02-15 fixed gaps in pcb outline
2021-02-15 looking at filling
2021-02-16 pre-updating gnd
2021-02-16 adding copper fill
2021-02-16 readded missing silkscreen text
2021-02-16 added signature
2021-02-17 added styled lines to top
2021-02-17 started with bottom plate
2021-02-19 finished designing bottom plate
2021-02-19 finished mounting plate
2021-02-19 fixed silkscreen on bottom plate
2021-02-19 update images and readme
2021-02-21 added ref placeholders and created gerbers
2021-03-14 changed bottom glasses to cu
2021-03-17 added sun footprint
2021-03-23 added swanky sun (imho)
2021-03-23 created new gerbers for bototm
2021-04-15 created drawings for top window
2021-04-15 combined window drawings
2021-04-17 create build log
2021-04-19 update build log
2021-04-20 update build log and readme
2021-04-20 more updates and some spell checking
2021-04-26 added photoshoot photos
2021-04-26 added photos to readme
2021-05-01 updated readme and build log
2021-05-03 updated readme title
2021-05-03 updated photoshoot images and added link
2021-05-03 fix link
2021-08-22 linked to qmk firmware in readme
2021-08-24 updated docs with release
2021-08-24 updated build log
2021-08-24 removed gerbers
2021-08-24 rearranged kicad folder
2021-08-26 added empty schematics files for bottom and top plate
2021-08-26 updated gh action
2021-08-26 update kibot config and gh action
2021-08-26 updated kibot file
